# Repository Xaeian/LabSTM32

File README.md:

# Nucleo Base Project

Bazowy projekt dla procesorów `STM32` z rodziny `G0`. Zawiera on wszystkie pliki nagłówkowe

###Struktura projektu

+ Inc
  + CMSIS - pliki nagłówkowe od ARM
  + ST - pliki nagłówkowe od ST
+ **Scr** - katalog z naszymi plikami
  + `main.c` - plik główny
  + `syscalls.c`
  + `sysmem.c` (plik główny)
+ Startup
  - `startup_stm32g081rbtx.s` - plik inicjacyjny
+ `STM32G081RBTx_Flash.ld` - plik struktury pamięci

W projekcie zaimplementowane są pliki pliki dla procesora **STM32G081xx** jednak równie dobrze działają dla procesorów **STM32G071xx**. Mikrokontroler **STM32G070xx** nie posiada wszystkich peryferiów, więc niektórych definicji nie należy używać.

Projekt obsługuje wersję procesorów z **128kB** pamięci **FLASH** oraz **36kB** pamięci **RAM**. W przypadku innych konfiguracji konieczna jest podmiana pliku `STM32G081RBTx_Flash.ld`

Program startowy z częstotliowścią 400ms miga diodą podpiędą do pinu **PA5** na płytce **NUCLEO**.

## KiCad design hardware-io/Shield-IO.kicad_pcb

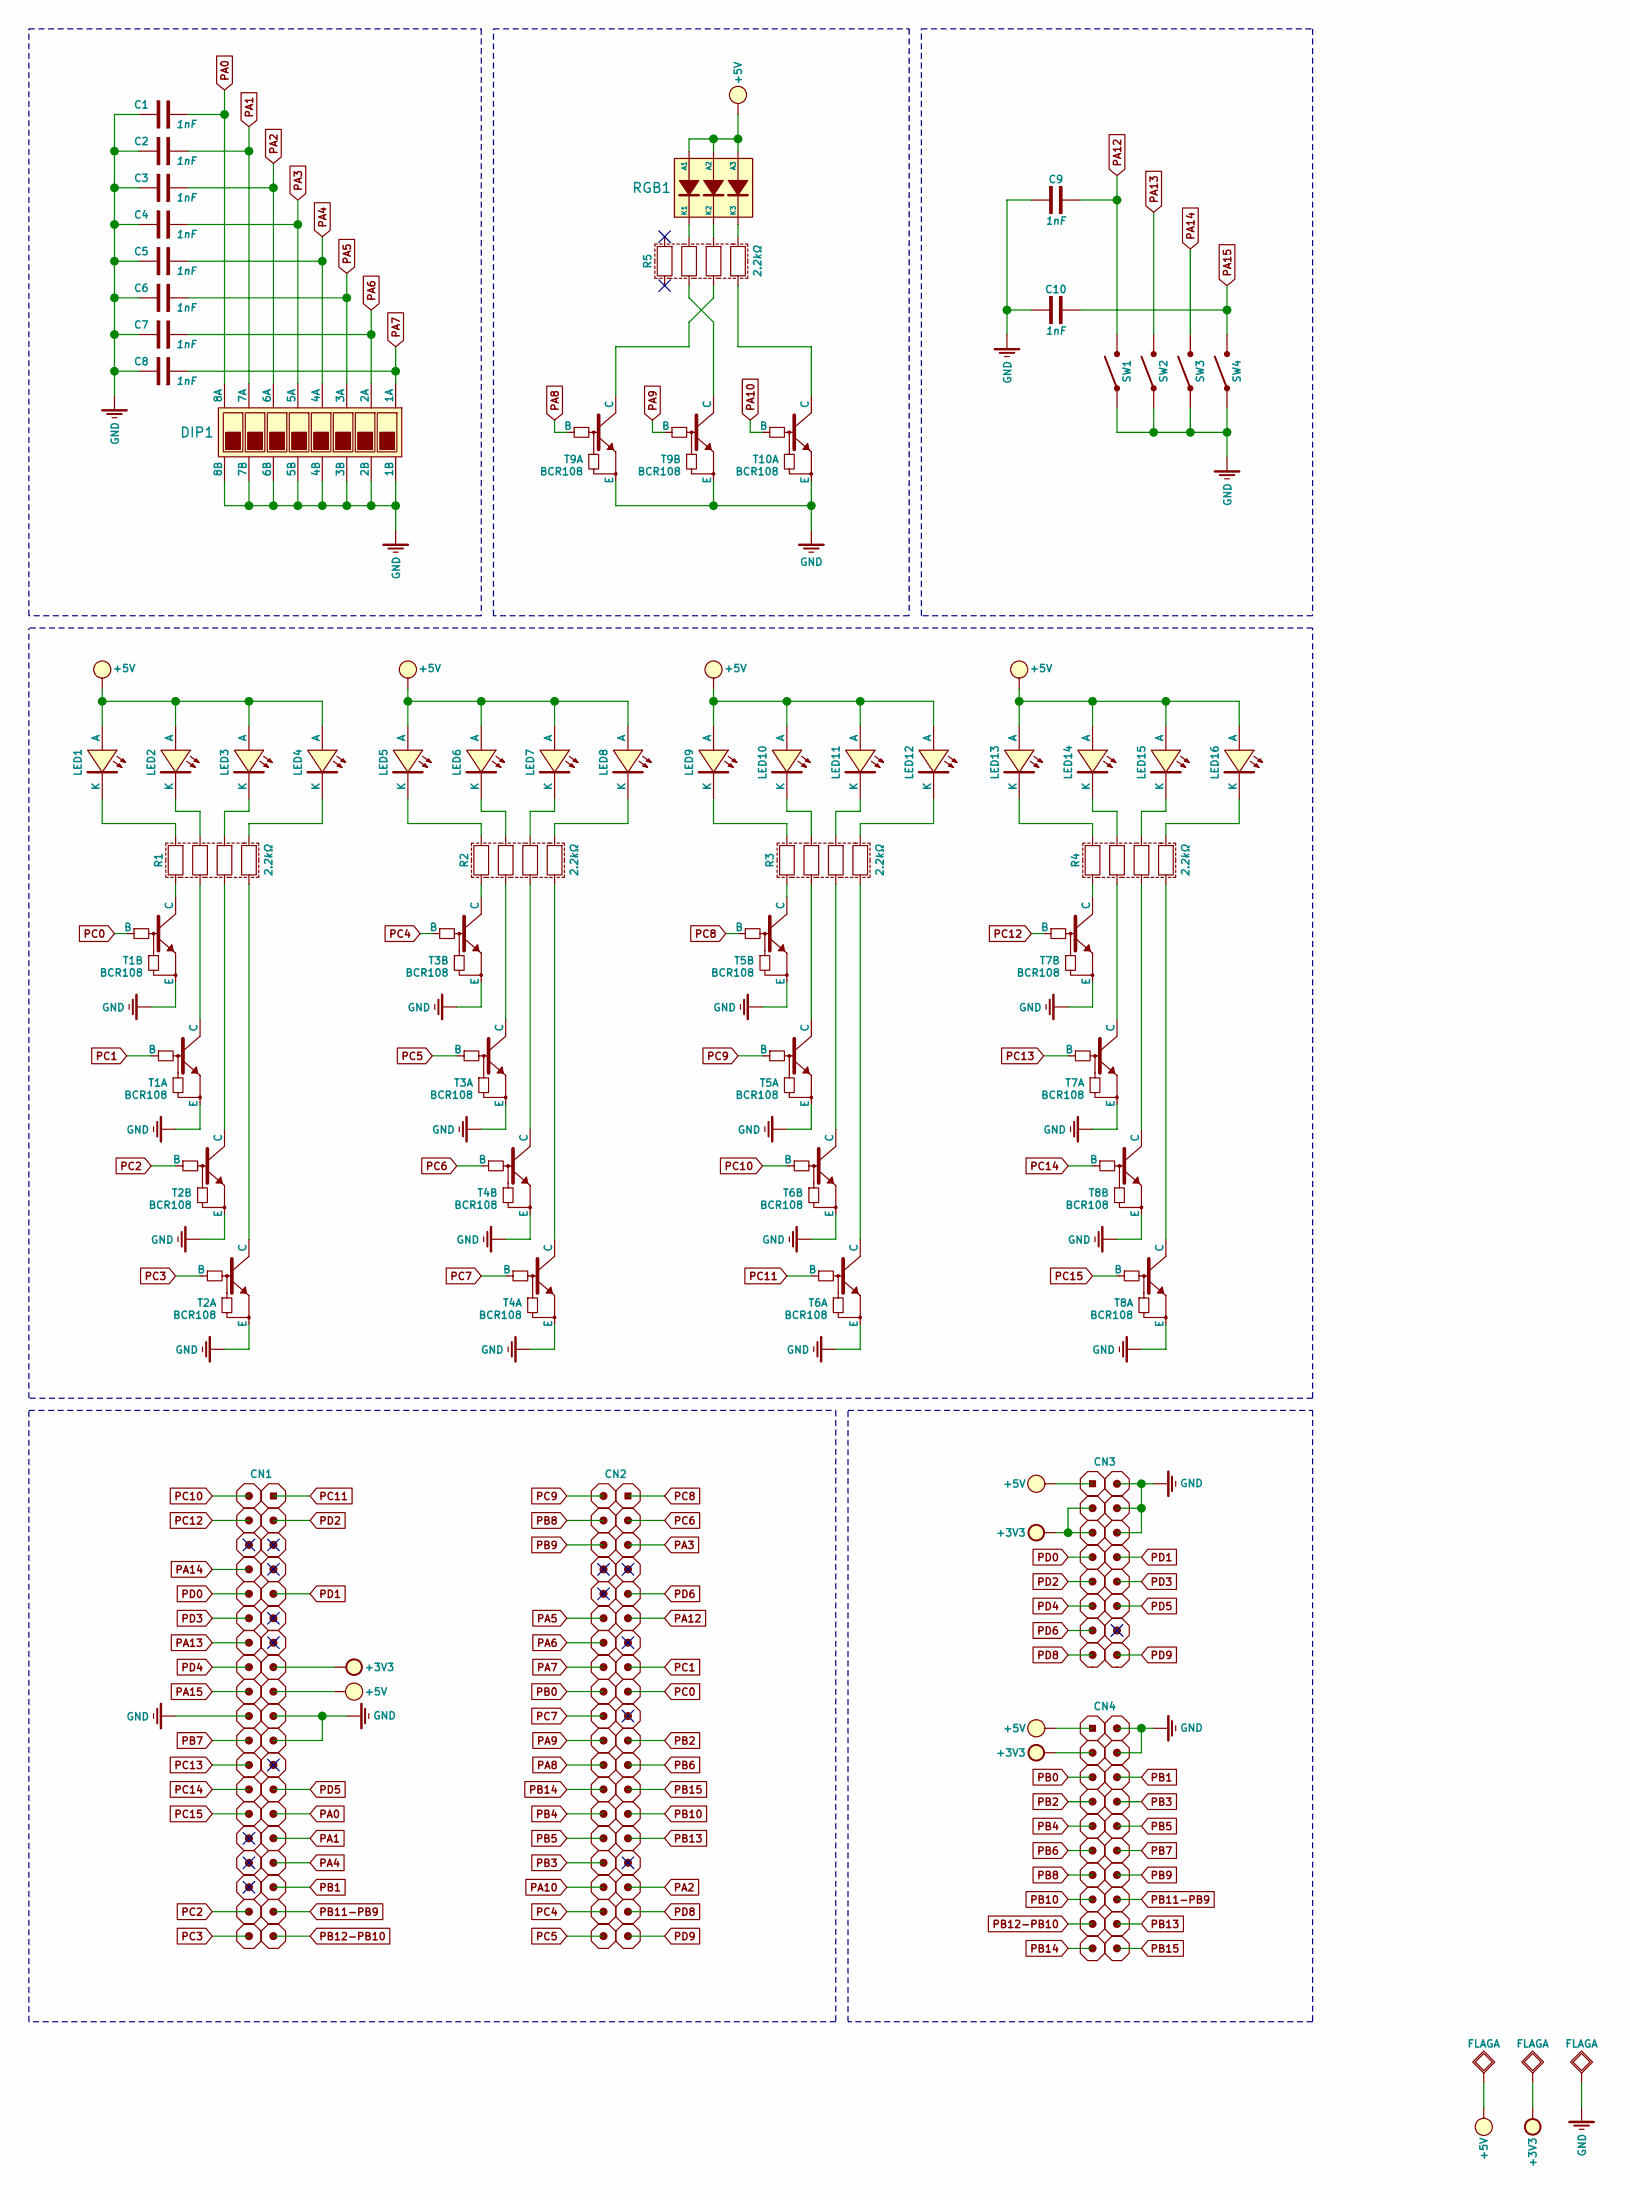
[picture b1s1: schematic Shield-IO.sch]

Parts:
C1, C2, C3, C4, C5, C6, C7, C8, C9, C10: 1nF; 0603
CN1, CN2: 2x19; THT-2.54-FS-2x19
CN3: 2x08; THT-2.54-MS-2x08
CN4: 2x10; THT-2.54-MS-2x10
DIP1: WS-DISV; SMD-DIP08
LED1, LED2, LED3, LED4, LED5, LED6, LED7, LED8, LED9, LED10, LED11, LED12, LED13, LED14, LED15, LED16: 3020; PLCC2-3020
R1, R2, R3, R4, R5: 2.2kΩ; 4x0603
RGB1: 5050; PLCC6-5050
SW1, SW2, SW3, SW4: TACT; 6.0x3.5
T1, T2, T3, T4, T5, T6, T7, T8, T9, T10: BCR108; SOT363-6

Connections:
+3V3: CN1.15, CN3.3, CN3.5, CN4.3
+5V: CN1.17, CN3.1, CN4.1, LED1.2 (A), LED2.2 (A), LED3.2 (A), LED4.2 (A), LED5.2 (A), LED6.2 (A), LED7.2 (A), LED8.2 (A), LED9.2 (A), LED10.2 (A), LED11.2 (A), LED12.2 (A), LED13.2 (A), LED14.2 (A), LED15.2 (A), LED16.2 (A), RGB1.1 (A1), RGB1.3 (A2), RGB1.5 (A3)
GND: C1.1, C2.1, C3.1, C4.1, C5.1, C6.1, C7.1, C8.1, C9.1, C10.1, CN1.19, CN1.20, CN1.21, CN3.2, CN3.4, CN3.6, CN4.2, CN4.4, DIP1.2 (1B), DIP1.4 (2B), DIP1.6 (3B), DIP1.8 (4B), DIP1.10 (5B), DIP1.12 (6B), DIP1.14 (7B), DIP1.16 (8B), SW1.1, SW2.1, SW3.1, SW4.1, T1.1 (E), T1.4 (E), T2.1 (E), T2.4 (E), T3.1 (E), T3.4 (E), T4.1 (E), T4.4 (E), T5.1 (E), T5.4 (E), T6.1 (E), T6.4 (E), T7.1 (E), T7.4 (E), T8.1 (E), T8.4 (E), T9.1 (E), T9.4 (E), T10.1 (E)
unnamed: LED1.1 (K), R1.7
unnamed: LED2.1 (K), R1.5
unnamed: LED3.1 (K), R1.3
unnamed: LED4.1 (K), R1.1
unnamed: LED5.1 (K), R2.7
unnamed: LED6.1 (K), R2.5
unnamed: LED7.1 (K), R2.3
unnamed: LED8.1 (K), R2.1
unnamed: LED9.1 (K), R3.7
unnamed: LED10.1 (K), R3.5
unnamed: LED11.1 (K), R3.3
unnamed: LED12.1 (K), R3.1
unnamed: LED13.1 (K), R4.7
unnamed: LED14.1 (K), R4.5
unnamed: LED15.1 (K), R4.3
unnamed: LED16.1 (K), R4.1
unnamed: R1.2, T2.6 (C)
unnamed: R1.4, T2.3 (C)
unnamed: R1.6, T1.6 (C)
unnamed: R1.8, T1.3 (C)
unnamed: R2.2, T4.6 (C)
unnamed: R2.4, T4.3 (C)
unnamed: R2.6, T3.6 (C)
unnamed: R2.8, T3.3 (C)
unnamed: R3.2, T6.6 (C)
unnamed: R3.4, T6.3 (C)
unnamed: R3.6, T5.6 (C)
unnamed: R3.8, T5.3 (C)
unnamed: R4.2, T8.6 (C)
unnamed: R4.4, T8.3 (C)
unnamed: R4.6, T7.6 (C)
unnamed: R4.8, T7.3 (C)
unnamed: R5.1, RGB1.6 (K3)
unnamed: R5.2, T10.6 (C)
unnamed: R5.3, RGB1.4 (K2)
unnamed: R5.4, T9.6 (C)
unnamed: R5.5, RGB1.2 (K1)
unnamed: R5.6, T9.3 (C)
PA0: C1.2, CN1.27, DIP1.15 (8A)
PA1: C2.2, CN1.29, DIP1.13 (7A)
PA2: C3.2, CN2.33, DIP1.11 (6A)
PA3: C4.2, CN2.5, DIP1.9 (5A)
PA4: C5.2, CN1.31, DIP1.7 (4A)
PA5: C6.2, CN2.12, DIP1.5 (3A)
PA6: C7.2, CN2.14, DIP1.3 (2A)
PA7: C8.2, CN2.16, DIP1.1 (1A)
PA8: CN2.24, T9.2 (B)
PA9: CN2.22, T9.5 (B)
PA10: CN2.34, T10.2 (B)
PA12: C9.2, CN2.11, SW1.2
PA13: CN1.14, SW2.2
PA14: CN1.8, SW3.2
PA15: C10.2, CN1.18, SW4.2
PB0: CN2.18, CN4.5
PB1: CN1.33, CN4.6
PB2: CN2.21, CN4.7
PB3: CN2.32, CN4.8
PB4: CN2.28, CN4.9
PB5: CN2.30, CN4.10
PB6: CN2.23, CN4.11
PB7: CN1.22, CN4.12
PB8: CN2.4, CN4.13
PB9: CN2.6, CN4.14
PB10: CN2.27, CN4.15
PB11-PB9: CN1.35, CN4.16
PB12-PB10: CN1.37, CN4.17
PB13: CN2.29, CN4.18
PB14: CN2.26, CN4.19
PB15: CN2.25, CN4.20
PC0: CN2.17, T1.5 (B)
PC1: CN2.15, T1.2 (B)
PC2: CN1.36, T2.5 (B)
PC3: CN1.38, T2.2 (B)
PC4: CN2.36, T3.5 (B)
PC5: CN2.38, T3.2 (B)
PC6: CN2.3, T4.5 (B)
PC7: CN2.20, T4.2 (B)
PC8: CN2.1, T5.5 (B)
PC9: CN2.2, T5.2 (B)
PC10: CN1.2, T6.5 (B)
PC11: CN1.1, T6.2 (B)
PC12: CN1.4, T7.5 (B)
PC13: CN1.24, T7.2 (B)
PC14: CN1.26, T8.5 (B)
PC15: CN1.28, T8.2 (B)
PD0: CN1.10, CN3.7
PD1: CN1.9, CN3.8
PD2: CN1.3, CN3.9
PD3: CN1.12, CN3.10
PD4: CN1.16, CN3.11
PD5: CN1.25, CN3.12
PD6: CN2.9, CN3.13
PD8: CN2.35, CN3.15
PD9: CN2.37, CN3.16

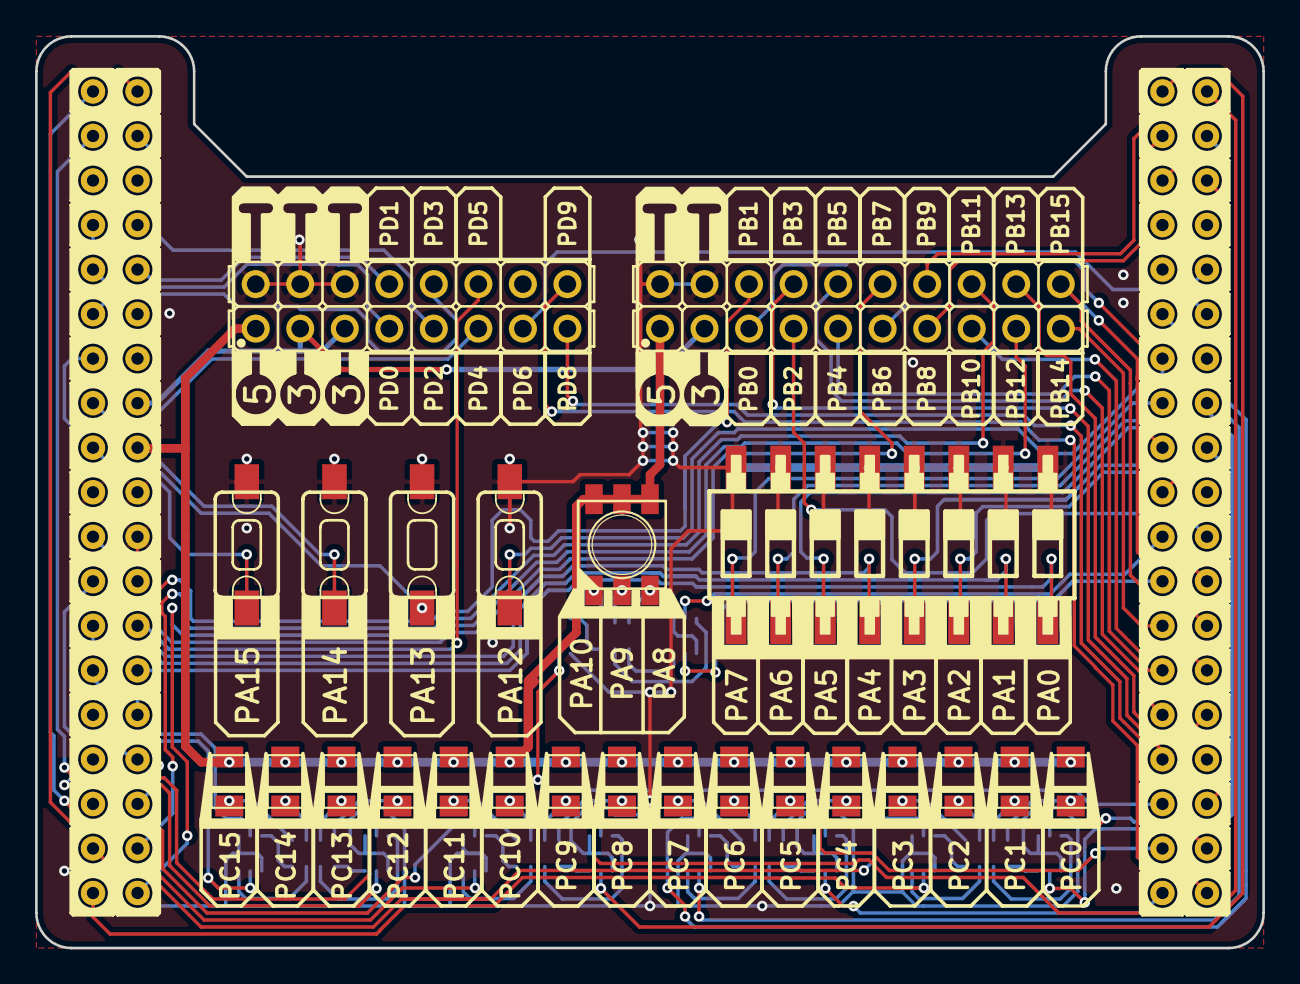
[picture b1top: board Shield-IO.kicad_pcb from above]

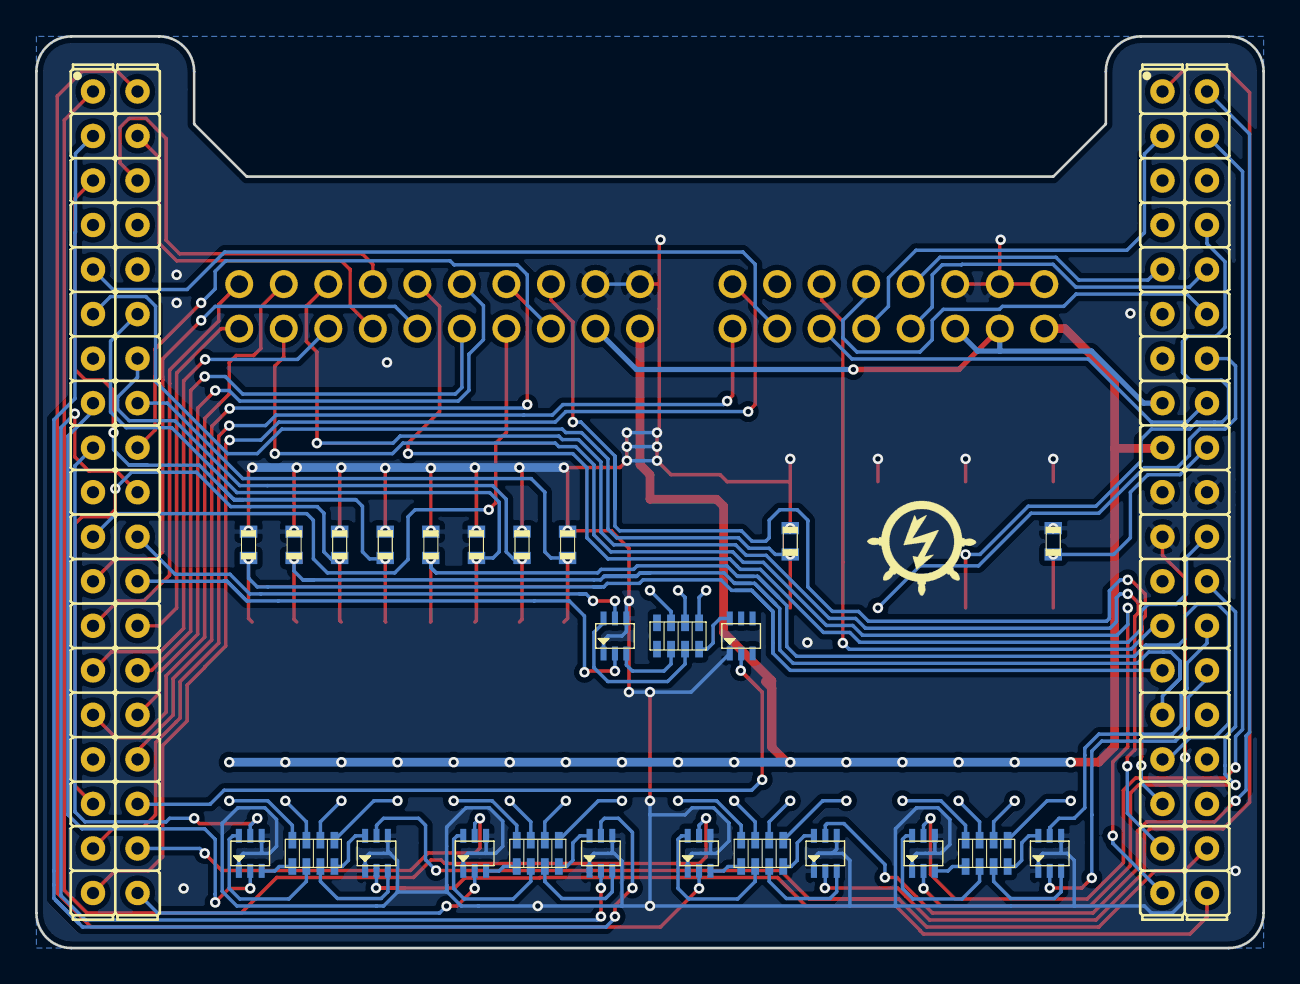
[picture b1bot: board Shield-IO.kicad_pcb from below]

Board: 2 copper layers, 70.0 x 52.0 mm, 118 parts (28 on the bottom side), 97 nets.

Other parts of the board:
3, 3#2, 3#3, 5, 5#2: LAB; Header-VCC
GND: LAB; Header-GND
GND#2, GND#3, GND#4, GND#5: LAB; Header-GND
IMG: Mask
IMG#2: Mask
IMG#3: LOGO; Logo
PA0, PA1, PA2, PA3, PA4, PA5, PA6, PA7: LAB; DIP
PA10: PA9; RGB
PA12, PA13, PA14, PA15: LAB; Button
PB0, PB1, PB2, PB3, PB4, PB5, PB6, PB7, PB8, PB9, PB10, PB11, PB12, PB13, PB14, PB15: LAB; Header
PC0, PC1, PC2, PC3, PC4, PC5, PC6, PC7, PC8, PC9, PC10, PC11, PC12, PC13, PC14, PC15: LAB; LED
PD0, PD1, PD2, PD3, PD4, PD5, PD6, PD8, PD9: LAB; Header

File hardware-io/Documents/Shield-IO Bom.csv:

Manufacturer|Value|Code|Pacage|Description|Count|Supplier|Datasheet|Reference|
Conntherm|2x19|PBD38S-CT|THT-2.54-FS-2x19|2.54mm;|2|Maritex|-|CN2; CN1|
Infineon Technologies|BCR108|BCR108SH6327|SOT363-6|50V; 500mA; 330mW; Reb:10kΩ; Rb:1kΩ;|10|TME|-|T10; T9; T1; T2; T8; T7; T6; T5; T4; T3|
Royal Ohm|2.2kΩ|4D03WGJ0222T5E|4x0603|±5%;|5|TME|-|R1; R2; R3; R4; R5|
Würth Elektronik|3020|150302YS73100|PLCC2-3020|Yellow;|16|Würth Elektronik|-|LED1; LED2; LED3; LED4; LED5; LED6; LED7; LED8; LED9; LED10; LED11; LED12; LED13; LED14; LED15; LED16|
Würth Elektronik|5050|150505M173300|PLCC6-5050|RGB;|1|Würth Elektronik|-|RGB1|
Würth Elektronik|2x08|61301621121|THT-2.54-MS-2x08|2.54mm;|1|Würth Elektronik|-|CN3|
Würth Elektronik|2x10|61302021121|THT-2.54-MS-2x10|2.54mm;|1|Würth Elektronik|-|CN4|
Würth Elektronik|WS-DISV|418121270808|SMD-DIP08|2.54mm;|1|Würth Elektronik|-|DIP1|
Würth Elektronik|TACT|434121043836|6.0x3.5|360g; 6.0x3.5x4.3mm;|4|Würth Elektronik|-|SW4; SW3; SW2; SW1|
Würth Elektronik|1nF|885012006063|0603|50V; NP0; 5%;|10|Würth Elektronik|-|C8; C7; C10; C9; C6; C5; C4; C3; C2; C1|

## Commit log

2020-10-14 init
2020-10-14 name
2020-10-16 void
2020-11-18 guide
2020-11-25 scheme
2020-12-02 reinit
2021-01-21 uart
2021-01-21 uart2
2022-04-04 nucleo
2022-04-11 struct
2022-04-11 gpio
2022-04-25 gpio-lib
2022-04-25 delay-lib
2022-04-25 begin
2022-04-26 links
2022-10-02 exti
2022-10-11 template
2022-10-16 hc595
2023-01-20 disp-7seg
2023-01-26 adc+disp+uart
